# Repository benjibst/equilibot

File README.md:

# equilibot
Self balancing robot with brushless motors

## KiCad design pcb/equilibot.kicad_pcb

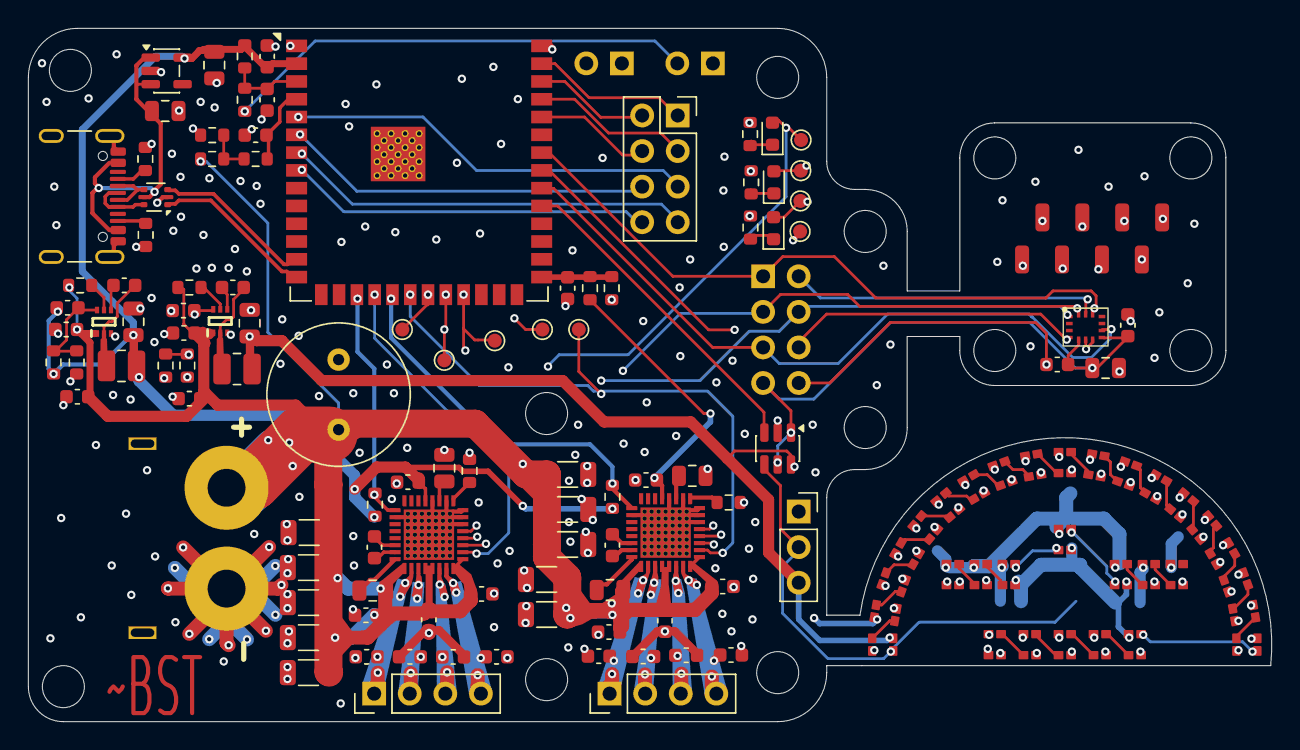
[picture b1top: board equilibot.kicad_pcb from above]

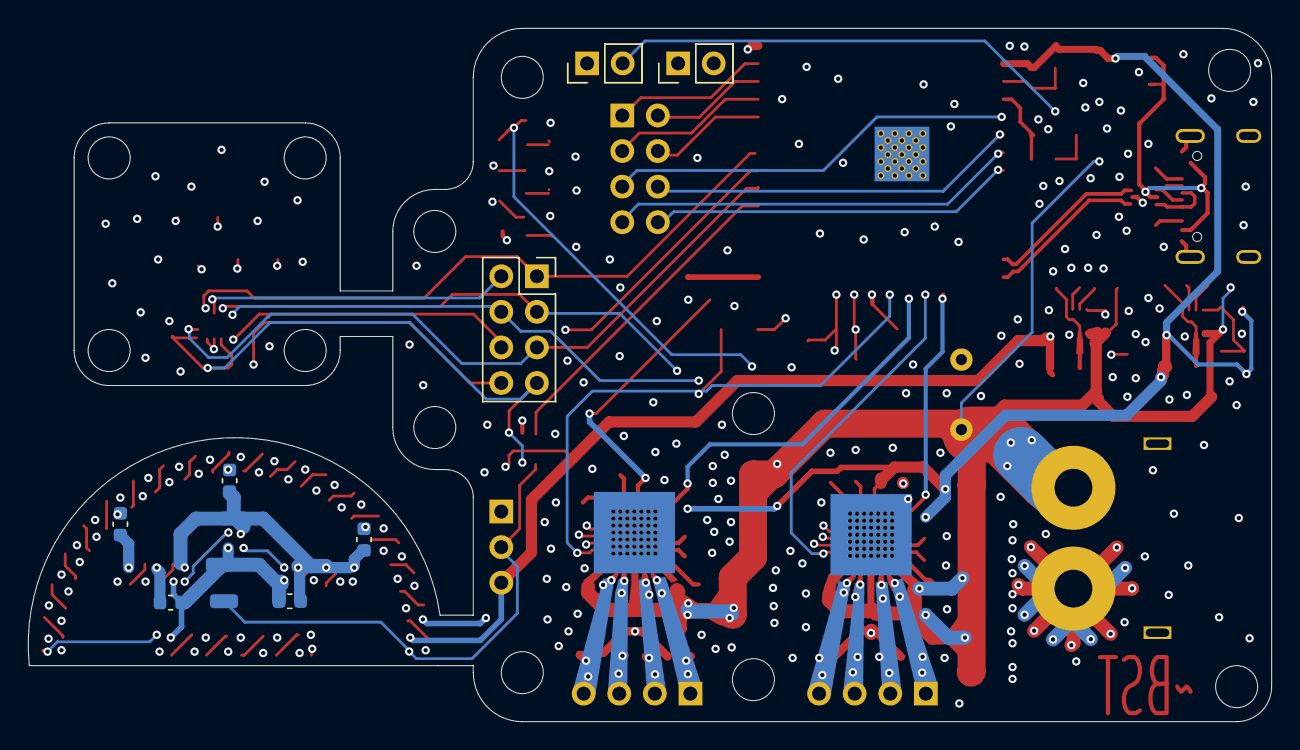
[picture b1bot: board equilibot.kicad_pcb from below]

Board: 4 copper layers, 88.8 x 49.5 mm, 153 parts (11 on the bottom side), 96 nets.

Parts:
C1, C2, C3, C4, C6, C12, C13, C14, C23, C24, C26, C30, C35, C53, C62, C63: 220n; C_0603_1608Metric
C5, C17, C34, C51, C52: 2.2u; C_0805_2012Metric
C7, C8, C9, C10, C18, C19, C20, C21: 470p; C_0603_1608Metric
C11, C22, C54, C55, C56, C57, C58, C59, C60, C61: 22u; C_1206_3216Metric
C15, C28: 1u; C_0805_2012Metric
C16, C29: 22n; C_0603_1608Metric
C25: 470u; C_Radial_D10.0mm_H16.0mm_P5.00mm
C27, C64: 10u; C_0603_1608Metric
C31, C36: 22u; C_0805_2012Metric
C32, C37, C39, C40, C41, C42, C48: 100n; C_0603_1608Metric
C33, C38: 47p; C_0603_1608Metric
D1, D2, D3, D4, D5, D6, D7, D8, D9, D10, D11, D12, D13, D14, D15, D16, D17, D18, D19, D20, D21, D22, D23, D24, D25, D26, D27, D28, D29, D30, D31: WS2812B; XL_WS2812B_0807
D32, D33, D34: LED_Small; LED_0603_1608Metric
IC1, IC2: TMC5240
IC3, IC4: TPS561243DRLR; SOTFL50P160X60-6N
J1: Conn_01x02_Socket; AMASS_XT60PW-M_1x02_P7.20mm_Horizontal
J2: USB_C_Receptacle_USB2.0_16P; USB_C_Receptacle_GCT_USB4105-xx-A_16P_TopMnt_Horizontal
J3, J4: Conn_01x04_Pin; PinHeader_1x04_P2.54mm_Vertical
J5: Conn_01x03_Pin; PinSocket_1x03_P2.54mm_Vertical
J7, J8: Conn_01x08_Pin; PinSocket_2x04_P2.54mm_Vertical
L1, L2: 3.3u; L_1008_2520Metric
MT1: ICM-42670-P; XDCR_ICM-42670-P
R1, R4: 100; R_0603_1608Metric
R2, R3, R6, R9, R12: 5.6k; R_0603_1608Metric
R5: 12k; R_0603_1608Metric
R7, R11: 3k; R_0603_1608Metric
R8: 10k; R_0603_1608Metric
R10, R16: 13k; R_0603_1608Metric
R13, R17: 100k; R_0603_1608Metric
R14: 135k; R_0603_1608Metric
R15, R19: 30k; R_0603_1608Metric
R18: 220k; R_0603_1608Metric
R20, R21: 5.1k; R_0603_1608Metric
R22: 1k; R_0603_1608Metric
SW1, SW2: SW_Push; PinHeader_1x02_P2.54mm_Vertical
TP1, TP2, TP3, TP4, TP5, TP6, TP7, TP9, TP10: TestPoint; TestPoint_Pad_D1.0mm
TP8, TP11, TP12, TP13, TP14, TP15, TP16, TP17, TP18, TP19, TP20: TestPoint; TestPoint_Pad_1.0x1.0mm
U1: ESP32-S3-WROOM-1
U2: SN74LVC1T45DBV; SOT-23-6
U3: USBLC6-2P6; SOT-666
U4: TLV75533PDBV; SOT-23-5

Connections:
/3V3: C4.2, C5.2, C6.1, C14.2, C26.2, C31.1, C33.2, C52.2, C53.2, D34.2 (A), IC1.5 (VCC_IO), IC2.5 (VCC_IO), J7.7, L1.1, MT1.5 (VDDIO), MT1.8 (VDD), R2.1, R3.1, R9.2, R12.2, R14.2, TP2.1, TP19.1, U1.2 (3V3), U2.1 (VCCA), U2.5 (DIR), U4.5 (OUT)
/5V: C36.1, C38.2, C39.2, C40.2, C41.2, C42.2, C48.2, D1.4 (5V), D2.4 (5V), D3.4 (5V), D4.4 (5V), D5.4 (5V), D6.4 (5V), D7.4 (5V), D8.4 (5V), D9.4 (5V), D10.4 (5V), D11.4 (5V), D12.4 (5V), D13.4 (5V), D14.4 (5V), D15.4 (5V), D16.4 (5V), D17.4 (5V), D18.4 (5V), D19.4 (5V), D20.4 (5V), D21.4 (5V), D22.4 (5V), D23.4 (5V), D24.4 (5V), D25.4 (5V), D26.4 (5V), D27.4 (5V), D28.4 (5V), D29.4 (5V), D30.4 (5V), D31.4 (5V), D33.2 (A), J5.3, L2.1, R18.2, TP3.1, TP11.1, U2.6 (VCCB)
/BAT_MON: C3.2, R6.2, U1.4 (IO4)
/IMU_INT1: J7.6, MT1.4 (INT1/INT), TP18.1, U1.33 (IO40)
/IMU_INT2: J7.5, MT1.9 (INT2), TP17.1, U1.32 (IO39)
/IO5: J8.5, U1.5 (IO5)
/IO6: J8.6, U1.6 (IO6)
/IO7: J8.7, U1.7 (IO7)
/IO15: J8.8, U1.8 (IO15)
/LED_DIN: U1.31 (IO38), U2.3 (A)
/SPI_CS_IMU: J7.1, MT1.12 (AP_CS), TP12.1, U1.34 (IO41)
/SPI_CS_STP1: IC2.26 (CSN/AD2), TP10.1, U1.20 (IO12)
/SPI_CS_STP2: IC1.26 (CSN/AD2), TP9.1, U1.18 (IO10)
/SPI_MISO: IC1.29 (SDO/NAO), IC2.29 (SDO/NAO), J7.4, MT1.1 (AP_SDO/AP_AD0), TP6.1, TP15.1, U1.21 (IO13)
/SPI_MOSI: IC1.28 (SDI/AD0), IC2.28 (SDI/AD0), J7.3, MT1.14 (AP_SDA/AP_SDIO/AP_SDI), TP5.1, TP14.1, U1.22 (IO14)
/SPI_SCLK: IC1.27 (SCK/AD1), IC2.27 (SCK/AD1), J7.2, MT1.13 (AP_SCL/AP_SCLK), TP4.1, TP13.1, U1.23 (IO21)
/STP1_DRV_EN: IC2.9 (DRV_ENN), R12.1, U1.19 (IO11)
/STP2_DRV_EN: IC1.9 (DRV_ENN), R9.1, U1.17 (IO9)
/USB_N: U1.13 (USB_D-), U3.3 (I/O2)
/USB_P: U1.14 (USB_D+), U3.1 (I/O1)
/VM: C11.1, C12.2, C13.2, C15.2, C22.1, C23.2, C24.2, C25.1, C27.1, C28.2, C30.2, C35.2, C54.1, C55.1, C56.1, C57.1, C58.1, C59.1, C60.1, C61.1, C62.2, C63.2, C64.1, D32.2 (A), IC1.17 (VS), IC1.20 (VS), IC1.21 (VS), IC1.24 (VS), IC1.25 (SLEEPN), IC2.17 (VS), IC2.20 (VS), IC2.21 (VS), IC2.24 (VS), IC2.25 (SLEEPN), IC3.1 (VIN), IC4.1 (VIN), J1.2, R5.2, R13.2, R17.2, TP1.1
/leds/DIN_5V: D1.3 (DIN), J5.2, TP16.1, U2.4 (B)
/leds/O1: D12.1 (DOUT), D13.3 (DIN)
/leds/O2: D24.1 (DOUT), D25.3 (DIN)
/psu/SW3V3: C32.2, IC3.4 (BST)
/psu/SW5V: C37.2, IC4.4 (BST)
GND: C1.1, C2.1, C3.1, C4.1, C5.1, C6.2, C7.1, C8.2, C9.1, C10.2, C11.2, C12.1, C13.1, C14.1, C17.2, C18.1, C19.2, C20.1, C21.2, C22.2, C23.1, C24.1, C25.2, C26.1, C27.2, C30.1, C31.2, C34.2, C35.1, C36.2, C39.1, C40.1, C41.1, C42.1, C48.1, C51.1, C52.1, C53.1, C54.2, C55.2, C56.2, C57.2, C58.2, C59.2, C60.2, C61.2, C62.1, C63.1, C64.2, D1.2 (GND), D2.2 (GND), D3.2 (GND), D4.2 (GND), D5.2 (GND), D6.2 (GND), D7.2 (GND), D8.2 (GND), D9.2 (GND), D10.2 (GND), D11.2 (GND), D12.2 (GND), D13.2 (GND), D14.2 (GND), D15.2 (GND), D16.2 (GND), D17.2 (GND), D18.2 (GND), D19.2 (GND), D20.2 (GND), D21.2 (GND), D22.2 (GND), D23.2 (GND), D24.2 (GND), D25.2 (GND), D26.2 (GND), D27.2 (GND), D28.2 (GND), D29.2 (GND), D30.2 (GND), D31.2 (GND), IC1.2 (AIN), IC1.4 (AGND), IC1.10 (UART_EN), IC1.30 (CLK), IC1.31 (REFL), IC1.32 (REFR), IC1.33 (EP), IC2.2 (AIN), IC2.4 (AGND), IC2.10 (UART_EN), IC2.30 (CLK), IC2.31 (REFL), IC2.32 (REFR), IC2.33 (EP), IC3.3 (GND), IC4.3 (GND), J1.1, J2.A1 (GND), J2.A12 (GND), J2.B1 (GND), J2.B12 (GND), J2.S1 (SHIELD), J5.1, J7.8, MT1.6 (GND), MT1.7 (FSYNC), R7.1, R8.2, R10.2, R11.2, R15.1, R16.2, R19.1, R20.1, R21.1, R22.2, SW1.1, SW2.1, TP7.1, TP8.1, TP20.1, U1.1 (GND), U1.40 (GND), U1.41 (EP), U2.2 (GND), U3.2 (GND), U4.2 (GND)
unnamed: D1.1 (DOUT), D2.3 (DIN)
unnamed: D2.1 (DOUT), D3.3 (DIN)
unnamed: D3.1 (DOUT), D4.3 (DIN)
unnamed: D4.1 (DOUT), D5.3 (DIN)
unnamed: D5.1 (DOUT), D6.3 (DIN)
unnamed: D6.1 (DOUT), D7.3 (DIN)
unnamed: D7.1 (DOUT), D8.3 (DIN)
unnamed: D8.1 (DOUT), D9.3 (DIN)
unnamed: D9.1 (DOUT), D10.3 (DIN)
unnamed: D10.1 (DOUT), D11.3 (DIN)
unnamed: D11.1 (DOUT), D12.3 (DIN)
unnamed: D13.1 (DOUT), D14.3 (DIN)
unnamed: D14.1 (DOUT), D15.3 (DIN)
unnamed: D15.1 (DOUT), D16.3 (DIN)
unnamed: D16.1 (DOUT), D17.3 (DIN)
unnamed: D17.1 (DOUT), D18.3 (DIN)
unnamed: D18.1 (DOUT), D19.3 (DIN)
unnamed: D19.1 (DOUT), D20.3 (DIN)
unnamed: D20.1 (DOUT), D21.3 (DIN)
unnamed: D21.1 (DOUT), D22.3 (DIN)
unnamed: D22.1 (DOUT), D23.3 (DIN)
unnamed: D23.1 (DOUT), D24.3 (DIN)
unnamed: D25.1 (DOUT), D26.3 (DIN)
unnamed: D26.1 (DOUT), D27.3 (DIN)
unnamed: D27.1 (DOUT), D28.3 (DIN)
unnamed: D28.1 (DOUT), D29.3 (DIN)
unnamed: D29.1 (DOUT), D30.3 (DIN)
unnamed: D30.1 (DOUT), D31.3 (DIN)
unnamed: D32.1 (K), R8.1
unnamed: D33.1 (K), R11.1
unnamed: D34.1 (K), R22.1
unnamed: C16.1, IC1.14 (CPI)
unnamed: C16.2, IC1.15 (CPO)
unnamed: IC1.1 (IREF), R10.1
unnamed: C7.2, IC1.23 (OUT1A), J3.4
unnamed: C8.1, IC1.18 (OUT1B), J3.1
unnamed: C9.2, IC1.22 (OUT2A), J3.3
unnamed: C10.1, IC1.19 (OUT2B), J3.2
unnamed: C15.1, IC1.16 (VCP)
unnamed: C17.1, IC1.3 (VDD_1V8)
unnamed: C29.1, IC2.14 (CPI)
unnamed: C29.2, IC2.15 (CPO)
unnamed: IC2.1 (IREF), R16.1
unnamed: C18.2, IC2.23 (OUT1A), J4.4
unnamed: C19.1, IC2.18 (OUT1B), J4.1
unnamed: C20.2, IC2.22 (OUT2A), J4.3
unnamed: C21.1, IC2.19 (OUT2B), J4.2
unnamed: C28.1, IC2.16 (VCP)
unnamed: C34.1, IC2.3 (VDD_1V8)
unnamed: IC3.5 (EN), R13.1
unnamed: C33.1, IC3.6 (FB), R14.1, R15.2
unnamed: C32.1, IC3.2 (SW), L1.2
unnamed: IC4.5 (EN), R17.1
unnamed: C38.1, IC4.6 (FB), R18.1, R19.2
unnamed: C37.1, IC4.2 (SW), L2.2
unnamed: J2.A5 (CC1), R20.2
unnamed: J2.B5 (CC2), R21.2
unnamed: J2.A6 (D+), J2.B6 (D+), U3.6 (I/O1)
unnamed: J2.A7 (D-), J2.B7 (D-), U3.4 (I/O2)
unnamed: J8.1, U1.39 (IO1)
unnamed: J8.2, U1.38 (IO2)
unnamed: J8.3, U1.37 (TXD0)
unnamed: J8.4, U1.36 (RXD0)
unnamed: R1.1, SW1.2
unnamed: R4.1, SW2.2
unnamed: R5.1, R6.1, R7.2
unnamed: C1.2, R1.2, R2.2, U1.3 (EN)
unnamed: C2.2, R3.2, R4.2, U1.27 (IO0)
unnamed: C51.2, J2.A4 (VBUS), J2.A9 (VBUS), J2.B4 (VBUS), J2.B9 (VBUS), U3.5 (VBUS), U4.1 (IN), U4.3 (EN)

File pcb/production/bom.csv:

Designator,Footprint,Quantity,Value,LCSC Part #
"C1, C12, C13, C14, C2, C23, C24, C26, C3, C30, C35, C4, C53, C6, C62, C63",0603,16,220n,C21120
"C10, C18, C19, C20, C21, C7, C8, C9",0603,8,470p,C1620
"C11, C22, C54, C55, C56, C57, C58, C59, C60, C61",1206,10,22u,C12891
"C15, C28",0805,2,1u,C28323
"C16, C29",0603,2,22n,C21122
"C17, C34, C5, C51, C52",0805,5,2.2u,C377773
"C27, C64",0603,2,10u,C96446
"C31, C36",0805,2,22u,C45783
"C32, C37",0603,2,100n,C14663
"C33, C38",0603,2,47p,C1671
"D1, D10, D11, D12, D13, D14, D15, D16, D17, D18, D19, D2, D20, D21, D22, D23, D24, D25, D26, D27, D28, D29, D3, D30, D31, D4, D5, D6, D7, D8, D9",XL_WS2812B_0807,31,WS2812B,C3646929
"IC1, IC2",TMC5240,2,TMC5240,C7494373
"IC3, IC4",SOTFL50P160X60-6N,2,TPS561243DRLR,C42040978
"L1, L2",1008,2,3.3u,C5832373
"R1, R4",0603,2,100,C22775
"R10, R16",0603,2,13k,C22797
"R11, R7",0603,2,3k,C4211
"R12, R2, R3, R6, R9",0603,5,5.6k,C23189
"R13, R17",0603,2,100k,C25803
"R15, R19",0603,2,30k,C22984
R18,0603,1,220k,C22961
"R20, R21",0603,2,5.1k,C23186
R22,0603,1,1k,C21190
R5,0603,1,12k,C22790
R8,0603,1,10k,C25804

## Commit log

2025-11-29 driver and buck converter layout
2025-12-02 routing
2025-12-02 add jlcpcb part numbers
2025-12-04 remove esp32 module from production
2025-12-05 change layout of extern led board to not show vias
2025-12-08 PRODUCTION
2026-02-12 c project
2026-02-12 let strip working
2026-02-14 abstraction for adressable leds
2026-02-14 add fork of esp bsp for spi communication with icm42670
2026-02-14 submodule update
2026-02-14 led strip example in separate file
2026-02-16 c++ library for icm42670
2026-02-18 remove submodule
2026-02-18 dashboard on website
2026-02-18 initial tmc5240 driver
2026-02-19 filtered data
2026-02-20 context for openclaw
2026-02-20 Add ICM42670 data-ready interrupt task and sample queue pipeline
2026-02-20 Add nlohmann/json submodule and use it for telemetry JSON serialization
2026-02-20 Revert batched websocket payloads; stream queued telemetry sample-by-sample
2026-02-21 consistent naming and performance
2026-02-21 imu configuration via web interface
2026-02-23 refactor
2026-02-23 awesome graphs
2026-02-25 orientation
2026-02-26 quaternion orientation on website
2026-03-01 kalman filter
2026-03-01 show tilt on leds
2026-03-03 configuration for spreadcycle on website
2026-03-14 refactor tmc
2026-03-29 pid controller for angle, not working yet
2026-03-29 controller website
2026-03-29 new json
2026-04-02 casaded pid controller
2026-04-07 add simscape model
2026-04-08 Remove project title and description from README
